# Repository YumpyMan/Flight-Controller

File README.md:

# Flight-Controller
Custom FC for my RC planes

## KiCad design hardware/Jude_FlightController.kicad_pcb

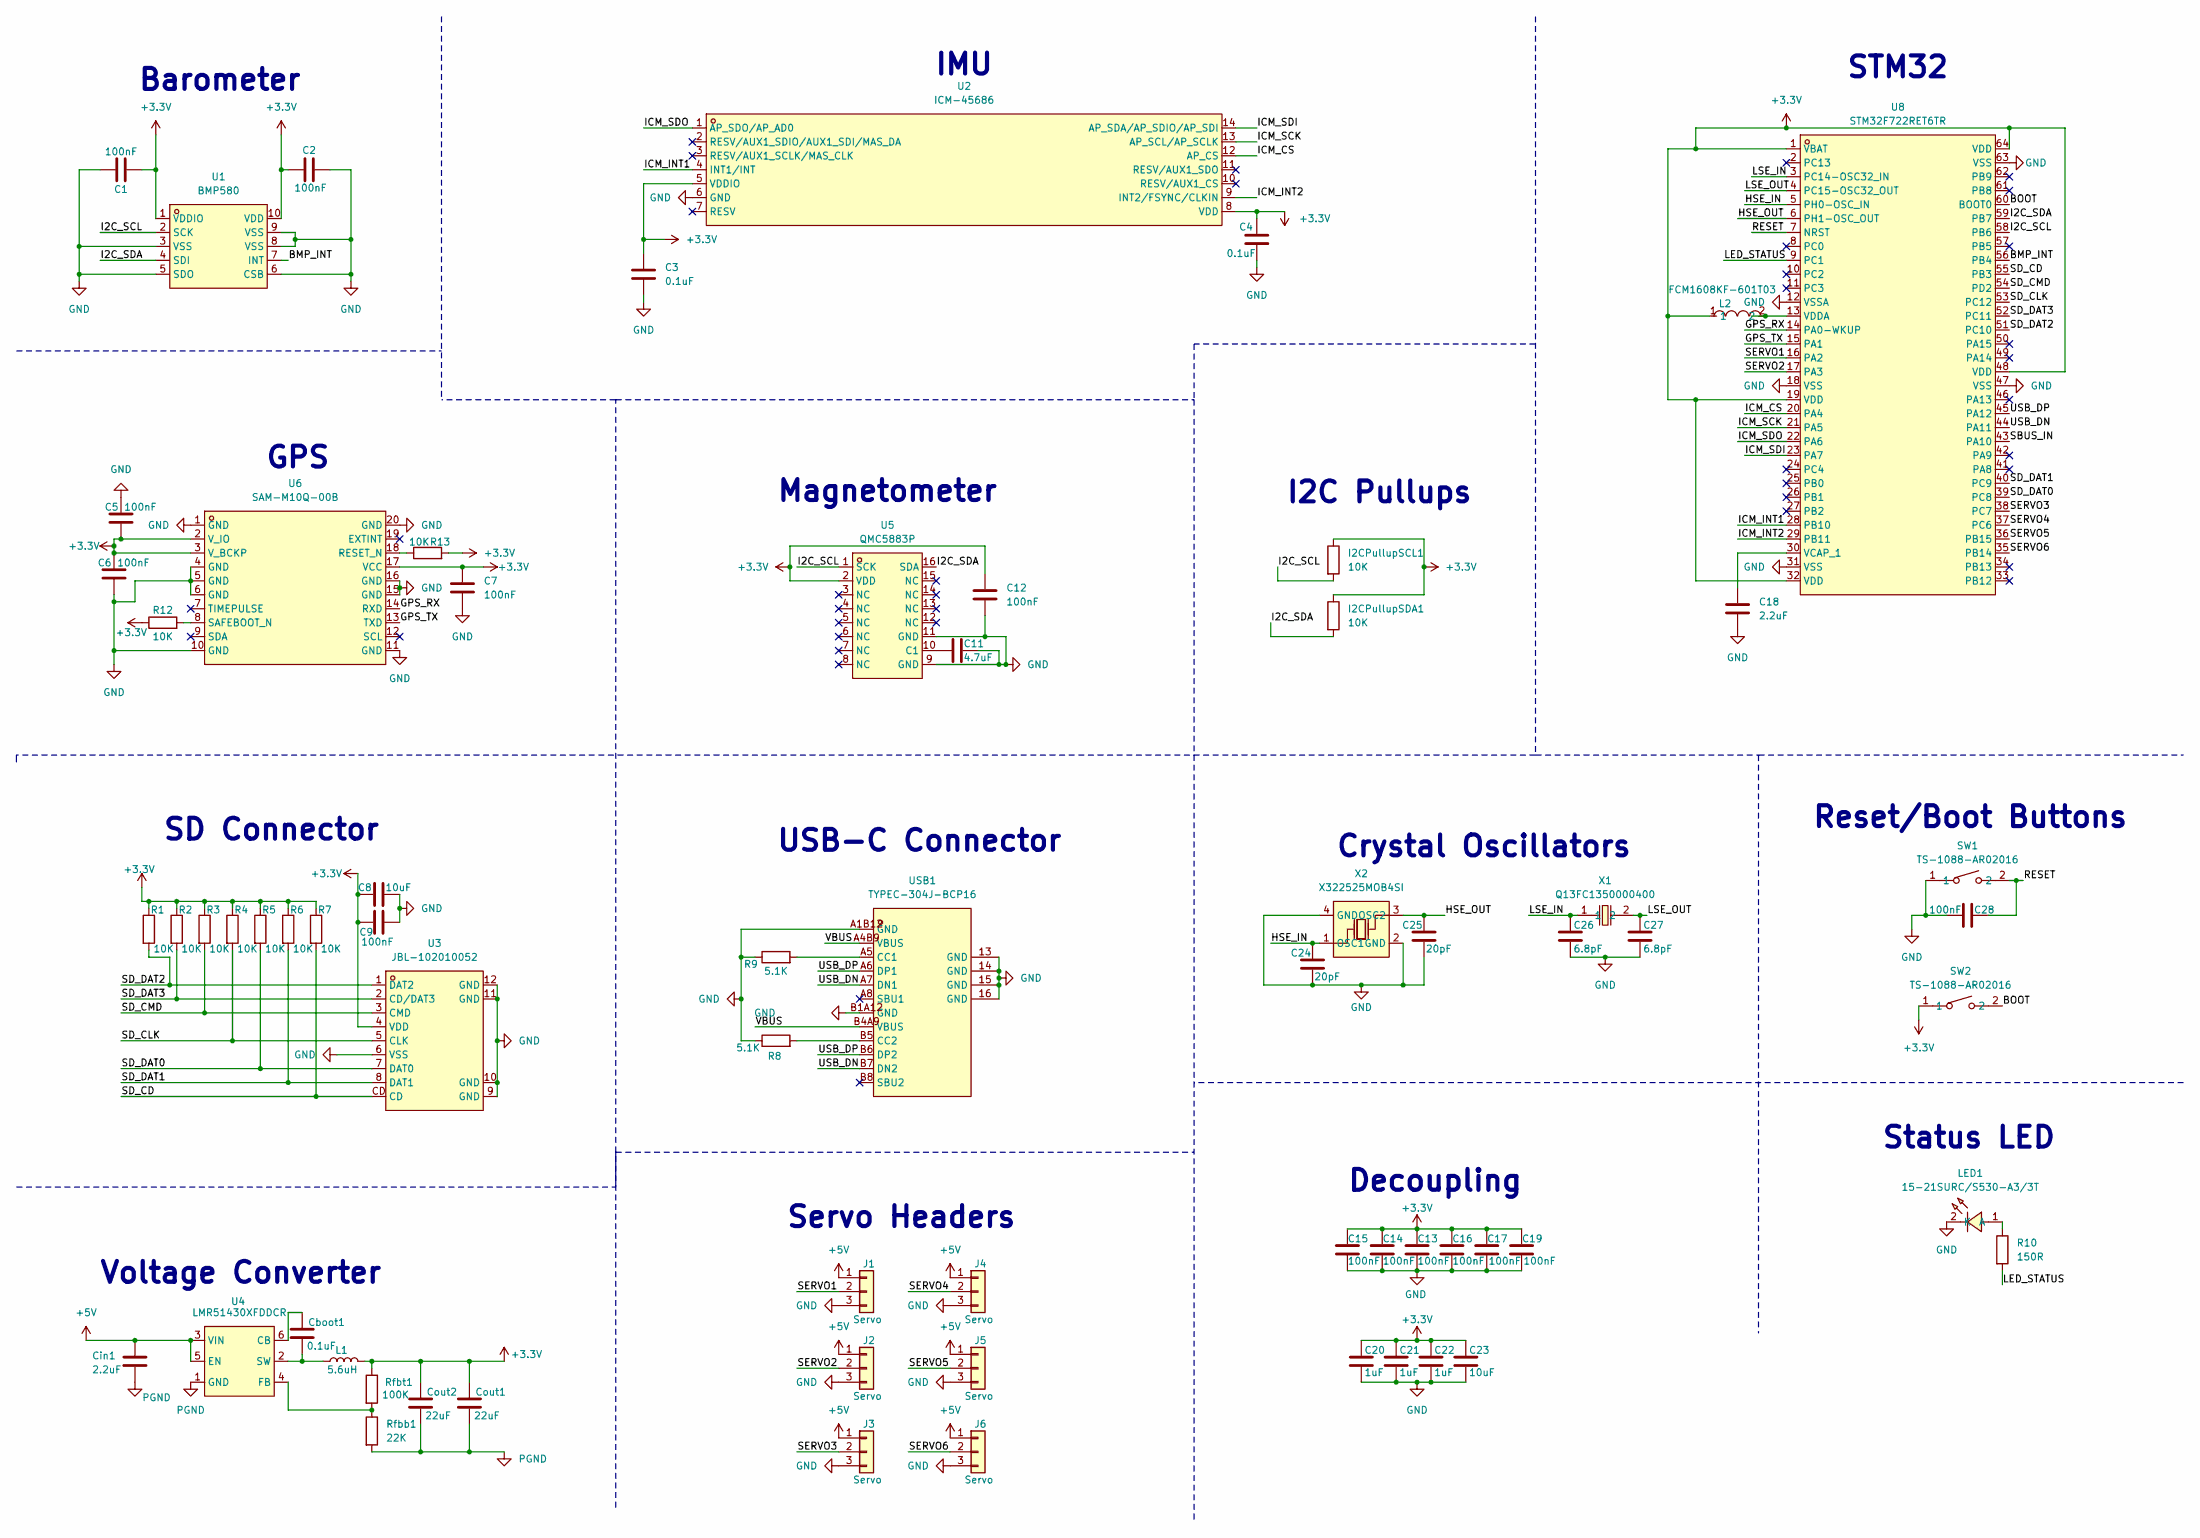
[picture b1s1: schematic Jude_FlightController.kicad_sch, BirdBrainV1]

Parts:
C1, C2, C5, C6, C7, C9, C12, C13, C14, C15, C16, C17, C19, C28: 100nF; C_01005_0402Metric
C3, C4: 0.1uF; C_01005_0402Metric
C8, C23: 10uF; C_0805_2012Metric
C11: 4.7uF; C_01005_0402Metric
C18: 2.2uF; C_01005_0402Metric
C20, C21, C22: 1uF; C_01005_0402Metric
C24, C25: 20pF; C_01005_0402Metric
C26, C27: 6.8pF; C_01005_0402Metric
Cboot1: 0.1uF; C_0402_1005Metric
Cin1: 2.2uF; C_0402_1005Metric
Cout1, Cout2: 22uF; C_0805_2012Metric
I2CPullupSCL1, I2CPullupSDA1: 10K; R_01005_0402Metric
J1, J2, J3, J4, J5, J6: Servo; PinHeader_1x03_P2.54mm_Vertical
L1: 5.6uH; IND-SMD_L3.0-W3.0
L2: FCM1608KF-601T03; L0603; MPN FCM1608KF-601T03; LCSC Part C141723
LED1: 15-21SURC/S530-A3/3T; LED_0402_1005Metric; MPN 15-21SURC/S530-A3/3T; LCSC Part C2984265
R1, R2, R3, R4, R5, R6, R7, R12, R13: 10K; R_01005_0402Metric
R8, R9: 5.1K; R_01005_0402Metric
R10: 150R; R_01005_0402Metric
Rfbb1: 22K; R_01005_0402Metric
Rfbt1: 100K; R_01005_0402Metric
SW1, SW2: TS-1088-AR02016; SW-SMD_L3.9-W3.0-P4.45; MPN TS-1088-AR02016; LCSC Part C720477
U1: BMP580; LGA-10_L2.0-W2.0-P0.50-TL_BMP580; MPN BMP580; LCSC Part C22391138
U2: ICM-45686; LGA-14_L3.0-W2.5-P0.50-TL; MPN ICM-45686; LCSC Part C22459454
U3: JBL-102010052; TF-CARD-SMD_JBL-102010052; MPN JBL-102010052; LCSC Part C49441431
U4: LMR51430XFDDCR; SOT-23-6_L2.9-W1.6-P0.95-LS2.8-BL; MPN LMR51430XDDCR; LCSC Part C5185863
U5: QMC5883P; LGA-16_L3.0-W3.0-P0.50-BL_SQ; MPN QMC5883P; LCSC Part C2847467
U6: SAM-M10Q-00B; LCC-20_L15.5-W15.5-P1.90_SAM-M10Q-00B; MPN SAM-M10Q-00B; LCSC Part C5443880
U8: STM32F722RET6TR; LQFP-64_10x10mm_P0.5mm; MPN STM32F722RET6TR; LCSC Part C3230927
USB1: TYPEC-304J-BCP16; USB-C-SMD_TYPEC-304J-BCP16; MPN TYPEC-304J-BCP16; LCSC Part C2835315
X1: Q13FC1350000400; FC-135R_L3.2-W1.5; MPN Q13FC13500004; LCSC Part C32346
X2: X322525MOB4SI; CRYSTAL-SMD_4P-L3.2-W2.5-BL; MPN X322525MOB4SI; LCSC Part C9006

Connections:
+3.3V: C1.2, C2.1, C3.1, C4.1, C5.2, C6.1, C7.1, C8.1, C9.1, C12.1, C13.1, C14.1, C15.1, C16.1, C17.1, C19.1, C20.1, C21.1, C22.1, C23.1, Cout1.1, Cout2.1, I2CPullupSCL1.1, I2CPullupSDA1.1, L1.2, L2.1, R1.1, R2.1, R3.1, R4.1, R5.1, R6.1, R7.1, R12.1, R13.2, Rfbt1.1, SW2.1, U1.1 (VDDIO), U1.10 (VDD), U2.5 (VDDIO), U2.8 (VDD), U3.4 (VDD), U5.2 (VDD), U6.2 (V_IO), U6.3 (V_BCKP), U6.17 (VCC), U8.1 (VBAT), U8.19 (VDD), U8.32 (VDD), U8.48 (VDD), U8.64 (VDD)
+5V: Cin1.1, J1.1, J2.1, J3.1, J4.1, J5.1, J6.1, U4.3 (VIN), U4.5 (EN)
/<NO NET>: R6.2, U3.8 (DAT1), U8.40 (PC9)
/BMP_INT: U1.7 (INT), U8.56 (PB4)
/BOOT: SW2.2, U8.60 (BOOT0)
/GPS_RX: U6.14 (RXD), U8.14 (PA0-WKUP)
/GPS_TX: U6.13 (TXD), U8.15 (PA1)
/HSE_IN: C24.1, U8.5 (PH0-OSC_IN), X2.1 (OSC1)
/HSE_OUT: C25.1, U8.6 (PH1-OSC_OUT), X2.3 (OSC2)
/I2C_SCL: I2CPullupSCL1.2, U1.2 (SCK), U5.1 (SCK), U8.58 (PB6)
/I2C_SDA: I2CPullupSDA1.2, U1.4 (SDI), U5.16 (SDA), U8.59 (PB7)
/ICM_CS: U2.12 (AP_CS), U8.20 (PA4)
/ICM_INT1: U2.4 (INT1/INT), U8.28 (PB10)
/ICM_INT2: U2.9 (INT2/FSYNC/CLKIN), U8.29 (PB11)
/ICM_SCK: U2.13 (AP_SCL/AP_SCLK), U8.21 (PA5)
/ICM_SDI: U2.14 (AP_SDA/AP_SDIO/AP_SDI), U8.23 (PA7)
/ICM_SDO: U2.1 (AP_SDO/AP_AD0), U8.22 (PA6)
/LED_STATUS: R10.2, U8.9 (PC1)
/LSE_IN: C26.1, U8.3 (PC14-OSC32_IN), X1.1
/LSE_OUT: C27.1, U8.4 (PC15-OSC32_OUT), X1.2
/RESET: C28.2, SW1.2, U8.7 (NRST)
/SBUS_IN: U8.43 (PA10)
/SD_CD: R7.2, U3.CD, U8.55 (PB3)
/SD_CLK: R4.2, U3.5 (CLK), U8.53 (PC12)
/SD_CMD: R3.2, U3.3 (CMD), U8.54 (PD2)
/SD_DAT0: R5.2, U3.7 (DAT0), U8.39 (PC8)
/SD_DAT2: R1.2, U3.1 (DAT2), U8.51 (PC10)
/SD_DAT3: R2.2, U3.2 (CD/DAT3), U8.52 (PC11)
/SERVO1: J1.2, U8.16 (PA2)
/SERVO2: J2.2, U8.17 (PA3)
/SERVO3: J3.2, U8.38 (PC7)
/SERVO4: J4.2, U8.37 (PC6)
/SERVO5: J5.2, U8.36 (PB15)
/SERVO6: J6.2, U8.35 (PB14)
/USB_DN: U8.44 (PA11), USB1.A7 (DN1), USB1.B7 (DN2)
/USB_DP: U8.45 (PA12), USB1.A6 (DP1), USB1.B6 (DP2)
/VBUS: USB1.A4B9 (VBUS), USB1.B4A9 (VBUS)
GND: C1.1, C2.2, C3.2, C4.2, C5.1, C6.2, C7.2, C8.2, C9.2, C11.2, C12.2, C13.2, C14.2, C15.2, C16.2, C17.2, C18.2, C19.2, C20.2, C21.2, C22.2, C23.2, C24.2, C25.2, C26.2, C27.2, C28.1, J1.3, J2.3, J3.3, J4.3, J5.3, J6.3, LED1.2 (K), R8.1, R9.1, SW1.1, U1.3 (VSS), U1.5 (SDO), U1.6 (CSB), U1.8 (VSS), U1.9 (VSS), U2.6 (GND), U3.6 (VSS), U3.9 (GND), U3.10 (GND), U3.11 (GND), U3.12 (GND), U5.9 (GND), U5.11 (GND), U6.1 (GND), U6.4 (GND), U6.5 (GND), U6.6 (GND), U6.10 (GND), U6.11 (GND), U6.15 (GND), U6.16 (GND), U6.20 (GND), U8.12 (VSSA), U8.18 (VSS), U8.31 (VSS), U8.47 (VSS), U8.63 (VSS), USB1.13 (GND), USB1.14 (GND), USB1.15 (GND), USB1.16 (GND), USB1.A1B12 (GND), USB1.B1A12 (GND), X2.2 (GND), X2.4 (GND)
unnamed: LED1.1 (A), R10.1
unnamed: Cboot1.1, U4.6 (CB)
unnamed: Rfbb1.1, Rfbt1.2, U4.4 (FB)
unnamed: Cboot1.2, L1.1, U4.2 (SW)
unnamed: C11.1, U5.10 (C1)
unnamed: R13.1, U6.18 (RESET_N)
unnamed: R12.2, U6.8 (SAFEBOOT_N)
unnamed: C18.1, U8.30 (VCAP_1)
unnamed: L2.2, U8.13 (VDDA)
unnamed: R9.2, USB1.A5 (CC1)
unnamed: R8.2, USB1.B5 (CC2)
PGND: Cin1.2, Cout1.2, Cout2.2, Rfbb1.2, U4.1 (GND)

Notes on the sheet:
Status LED
GPS
Crystal Oscillators
I2C Pullups
Reset/Boot Buttons
Voltage Converter
Servo Headers
Decoupling
Magnetometer
USB-C Connector
STM32
Barometer
IMU
SD Connector

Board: 2 copper layers, 68 parts (0 on the bottom side), 49 nets, no tracks yet.

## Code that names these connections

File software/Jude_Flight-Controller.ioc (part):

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Mcu.Name=STM32F722R(C-E)Tx
Mcu.Package=LQFP64
Mcu.UserName=STM32F722RETx
PA0-WKUP.Mode=Asynchronous
PA0-WKUP.Signal=UART4_TX
PA1.Mode=Asynchronous
PA1.Signal=UART4_RX
PA10.Mode=Asynchronous
PA10.Signal=USART1_RX
PA11.Mode=Device_Only
PA11.Signal=USB_OTG_FS_DM
PA12.Mode=Device_Only
PA12.Signal=USB_OTG_FS_DP
PA2.Signal=S_TIM9_CH1
PA3.Signal=S_TIM9_CH2
PA4.Mode=NSS_Signal_Hard_Output
PA4.Signal=SPI1_NSS
PA5.Mode=Full_Duplex_Master
PA5.Signal=SPI1_SCK
PA6.Mode=Full_Duplex_Master
PA6.Signal=SPI1_MISO
PA7.Mode=Full_Duplex_Master
PA7.Signal=SPI1_MOSI
PA9.Mode=Asynchronous
PA9.Signal=USART1_TX
PB10.GPIOParameters=GPIO_Label
PB10.GPIO_Label=ICM_INT1
PB10.Signal=GPXTI10
PB11.GPIOParameters=GPIO_Label
PB11.GPIO_Label=ICM_INT2
PB11.Signal=GPXTI11
PB14.Signal=S_TIM12_CH1
PB15.Signal=S_TIM12_CH2
PB3.GPIOParameters=GPIO_Label
PB3.GPIO_Label=SD_CD
PB3.Signal=GPIO_Input
PB4.GPIOParameters=GPIO_Label
PB4.GPIO_Label=BMP_INT
PB4.Signal=GPXTI4
PB6.Mode=I2C
PB6.Signal=I2C1_SCL
PB7.Mode=I2C
PB7.Signal=I2C1_SDA
PC10.Mode=SD_4_bits_Wide_bus
PC10.Signal=SDMMC1_D2
PC11.Mode=SD_4_bits_Wide_bus
PC11.Signal=SDMMC1_D3
PC12.Mode=SD_4_bits_Wide_bus
PC12.Signal=SDMMC1_CK
PC14-OSC32_IN.Mode=LSE-External-Oscillator
PC14-OSC32_IN.Signal=RCC_OSC32_IN
PC15-OSC32_OUT.Mode=LSE-External-Oscillator
PC15-OSC32_OUT.Signal=RCC_OSC32_OUT
PC6.Signal=S_TIM3_CH1
PC7.Signal=S_TIM3_CH2
PC8.Mode=SD_4_bits_Wide_bus
PC8.Signal=SDMMC1_D0
PC9.Mode=SD_4_bits_Wide_bus
PC9.Signal=SDMMC1_D1
PD2.Mode=SD_4_bits_Wide_bus
PD2.Signal=SDMMC1_CMD
PH0-OSC_IN.Mode=HSE-External-Oscillator
PH0-OSC_IN.Signal=RCC_OSC_IN
PH1-OSC_OUT.Mode=HSE-External-Oscillator
PH1-OSC_OUT.Signal=RCC_OSC_OUT
RCC.HSE_VALUE=25000000
board=custom

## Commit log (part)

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2026-06-18 initial project setup
2026-06-18 add KiCad project files
2026-06-19 imported component footprints from easyEDA
2026-06-26 updated schematic with wiring for IMU, barometer, SD, and voltage converter
2026-06-27 ignore .history folder
2026-06-29 added STM32CubeMX project files
2026-06-29 updated KiCad library with new components for MCU
2026-06-30 finished schematic with microcontroller and all supporting components
2026-06-30 organized schematic
